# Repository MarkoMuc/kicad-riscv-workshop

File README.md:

# ESP32 board workshop

- Uradni repozitorij: https://github.com/bulicp/FRI-ESP32-PCB-workshop/tree/main

- Postavimo shemo. Kjer grupiramo komponente glede na funkcionalnost.
- Preko USB + USB C konektor zelimo da napajamo vse komponente na sistemi (procesor, ledice, itd.)

## Dan 1: USB-C in vse potrebne povezave.

Izhodisce je `00-template` iz git repozitorija delavnice:
- `.PCB`: printed circuit board.
- `.SCH`: schemas. Dve shemi: power and digital + schema, ki ju zdruzi.

Zaceli bomo z power:
- USB C in konektorji.
- Lahko se uporablja za napajanje, nekateri procesorji tudi uporablja za flashanje, v ta namem rabimo USB del povezave, ne le napajanje.

Komponente vpeljemo iz knjiznice komponent, ostale dodamo: Simboli in footprint.
- Simbol je samo simbol (za sheme).
- Footprint je odtis komponent na tiskanem vezju (kje se lota, prostor, tloris komponente).

Pritisni `a`, da odpres izbiro/dodajanje simbolov.
Nasa knjiznica je `fri`.

Zacnemo z USB konektorjem `USC_C_Receptacle_USB2.0_16P` iz `fri`.
Rdece blazinice so kjer se zalota.
Vidimo 11 povezav, a jih je v resnici 16.
Predstavljene so s zicko, ki se konca s krogom.
To je zato, kjer `VBUS` ima v resnici vec povezav?

Pini na USB-C konektorju:
- `VBUS` signal je zica, ki bo dostavila 5V, za napajanje.
    - Za vsak vir naptosti nas zanimata dve stvari: tok in moc.
    - USB C standard doloca 3 napajalne moci:
        - Vsaj 500mA toka in 5V napteost = 2,5 W.
        - Ter se drugi dve.
    - Za nas bo 500mA dovolj, a velikokrat potrebujemo vec. Sistemo mora vedeti koliko mu lahko oddaja napajlni vir.
        Npr. ce ni dovolj napajanja, se sistem naj ne bi brizgal. Kako pa to lahko ve?
        - Imamo dva pina `CC1` in `CC2`. Povesta ali napajlnik dostavlja 500 mA ali vec.
- `CC1` in `CC2` sta analogna, ne digitalna.
    - Odjamalec more vedeti s cim ga napaja. Obratno napajalnik mora vedeti porabo (ponor?).
        Npr. da ni samo `VBUS-GRND` povezava?
    - Potrebujemo 2 upora za delovanje napajanje (zaradi standarda).
        Dodamo upor z imenom simbola `R`.
        Prvi je `5.1K` povezan na `CC1`, isto naredimo za `CC2`.
        Spodnja dela uporov povezemo na `GND`.
- `SHIELD` in `GND` povezem na zemljo. To je lahko isti konektor za `GND`, locimo zato, da se zice ne krizajo.
- `SBUS1` in `SBUS2` ne rabimo, a je to potrebno povedati KiCad, tako da oznacimo, da prikljucek ni povezan.
    Pritisnemo `q` in povezemo na prikljucek.
- `D` prikljucki so diferencialni (komplementarni) prikljucki. Ko prenasam `0` je na `D_+: 1` in na `D_-: 0` ter obratno.
    To opravimo zaradi vpliva zunanjih dejavnikov (in posledicnega induciranega toka).
    Ce se napetost poveca zaradi šuma, se podobno zgodi na drugih zicah v blizini => signali po diferencialnih parih.
    Tako lahko locimo med `0` in `1` kljub sumu.
    Na primer vedno opravimo: `D_+ - D_-`.
    Po odstevanju se šum odstani.
    Tu imamo 4 pine, pri USB-C lahko zato vstavimo kabel ne glede na orientacijo.
- `VBUS` ima pri nas 5V, povezemo ga preko zice, ki nadaljuje na drugem listu (drugi shemi).
    To naredimo tako, da zico oznacimo (label).

Za vsako komponento moramo poiskati `footprint` in povedat kaksen je footprint, da lahko tiskamo.
Za upornike izberemo `R_01005_0402Metric`:
    - `0402` pomeni velikost (sirina) fizicnega rezistorja. Manjsi ko je, manj inducirane napetosti?
    - `_SMD` pomeni: surface mount device.

Vse komponente na vezju se prelije s lakom, ki ni prevoden.
USB-C konektor ni prelit, in je iz kovine.
Vezje je potrebno zasciti pred elektrostaticnem naboju, ki bi poskodoval komponente.
Zagotavlja se s komponentami, ki preosmerijo ta naboj v `GND`.
To komponento postavimo na zico iz `VBUS`, ki se sprozi ko je napetost vec kot 5V.

Uprabimo diodo, ki v neki tocki, ne glede na velikost toka, napetost ne spreminja.
Povezemo diodo `PESD5V0S1UL` in jo obrnemo z `r`, povezemo naprej na `GND` (spodnji del) ter na `VBUS` zico.

"Induciran kondenzator" je posledica vec plastne strukture cipov in komponent (plasti silicija).
Iscemo komponento z zelo nizko kapacitivnost, saj kodenzator deformira PWL signale (kot so podatkovni).
Pri nas uporabimo za zascito USB komponente, `USBLC6-2SC6`, na sliko lahko vidimo interno diodo, ki sciti.
Prikljucka `1-6` ter `3-4` sta ista. `5` gre na `VBUS`, `2` gre na `GND`.
Povezemo na `D_-` in `D_+` (ter iste povezave skupaj), dodamo globalne labele (pazi na ime naj se konca enako, mislim da KICAD to potrebuje).

Neko osnovno analizo vezja opravimo z `inspect - ERC`, ki nas opozori, da ni elektricnega vira.
Da ga eksplicitno ustvarimo, dodamo `PWR_FLAG`. Podobno naredimo tudi za `GND` (t.j. minus).

Nasledjni korak je sprememba 5V toka v 3.3V, ki ga sprejme ESP32.
Uporabi se DC/DC pretvornike, regulatorje, transformerje?
Za pretvorbo naptosti uporabimo regulator `XC6220B331MR`:
- Regulator ima pin za kontrolo `CE-Chip Enable`, ki ga prizge.
    To se opravi npr. ko je premajhna napetost (prazna baterija, da jo zascitimo).
- Mi ne rabimo CE, zato povezemo na VBUS z upornikom, ki naj bi bil po standardu 10K ohm.
Datasheet pravi, da potrebujemo se 2 kondenzatorja, eden za vhod, eden za izhod.
Pri kondenzatorjih je tezko dosesti pripisano kapacitivnost.
Zelimo cim manjsi footprint, tezje je kontrolikarti kapacitivnost (zaradi segrevanja itd.).
Manjsi footprint pomeni manjsa induktivnost.
Izberemo footprint `0805SMD`.
Ustvarili smo LDO 3.3V regulator. Ker se mocno segrevajo, je potrebno pravilno postaviti, da se pasivno ohlaja.

Uprabimo lahko tudi DC-DC konvertorji, ki so brezizgubni (oddajo jo v kondenzator, ko jo rabijo dvigniti, jo vzamejo iz kondenzatorja).
Sestavljajo jih tuljave.
Vsi cipi, vkljucno z nasim esp32, imajo DC-DC konverter (realiziran na cipu).
Dovod elektricne moci lahko tudi sestavlja notranja baterija, ter sistem, ki izbira med baterijo in direktno povezavo.

Sedaj imamo vse kar rabimo, da povezemo CPE, premaknemo se na `digital` shemo.
V nasem primeru imamo `esp32-C3-mini`, ki je RISC-V procesor.
Sicer je to SoC, kar pomeni, da ni samo procesor, temvec je modul.
Vsebuje anteno (za WIFI ter BLE), sistem za flashanje, RAM, itd.
Pricljucki na `ESP32-C3-MINI-1`:
- `3V3` in `GND` povezemo na +3.3V in zemljo.
- `EN` povezemo na label `EN`.
- `GPIO18/19` povezemo na `USBD+/-` labele.
- `GPIO21/20` povezemo na `TXD/RXD` labele.
- `GPIO3-5` povezemo na isto imenske labele.
- `GPIO6/7` sta vezana na LED diode.
- `GPIO2 + GPIO8 + GPIO9` so pri ESP32 kontrolni signali, ki povejo, da rabi CPE poiskati novo vrednost is flasha (ki je bil spremenjen?) za zagon.
    Imenujemo `GPIOX_BOOT`.
- `GPIO10` povezemo na labelo `USER_BTN`.

Zaceli bomo z ledicami:
- Ledice so tudi diode, sveti ko je V1 > V2 (kjer je V1 na strani (stranice) trikotnika).
- `V2` stran vezemo na GPIO pin, ker je to stran, ki je manjsa. To pomeni, da iz pina ne vlece toka.
    Tako je ta pin ponor, energija gre v ohisje.
    Drugace bi od CPE zahtevali veliko napetosti?
    Ce vezemo drugo stran (V1) na 3.3V, je problem v tem, da ni nobene upornosti na povezavi. Tok je zato lahko velik in naredi skodo.
    Ta tok je treba omeijti (z uporom). Upor dolocimo glede na datasheet ledice (razpon uporov/tokov).
    Mi izberemo 330 ohmov, manj ko je upora, bolj je svetla ledica.
- Ponovimo isto za `LED1`.

Nadaljujemo z gumbom:
- Uporabimo `SW_Push`.
- Mi zelimo, da ob pritisku na gumb, zaznamo niclo: `USER_BTN`.
    To je zaradi tega, ker je lazje iti iz 1 v 0?
    Drugi del vezemo na 3.3V, ter na nek upornik (drugace je kratki stik).
    Tako je brez pritiska 3.3V, ko pa pritisnemo gumb, gremo iz 3.3 proti ground.
    Ta tok se le porabi (direktno v zemljo), zelimo cim manjsi upor?
    To je pull-up upornik.
    Manjsi ko je upor, vec je vpliva suma, a je manjsi tok?
    Vecji upor, manj vpliva suma, visji tok??
    Izberemo 10k ohm.
- Isto za `EN` gumb na cipu (reset gumb).

Pini GPIO2,8,9:
- Za zagon preko flasha, za prenos v flash, itd.
- GPIO2 vedno 1.
- GPIO8 vedno 1.
- Ce je po reset: GPIO9 high, preberi program v flash.
- Ce je po reset: GPIO9 low, potem se pripravi na branje iz USB.
- To pomeni, da je pametno GPIO9 vezati na nek gumb.
- GPIO2 in GPIO8 lahko vezemo na 3.3V, uporabimo tudi upornik kot v primeru gumba.

Ostale GPIO prikljucke zelimo vezati na GPIO pin, ker so splosni za uporabo:
- Uporabimo `Conn_01x08` za 8 pinov, mi imamo 7 pinov prostih.
- Vrstni red ni pomemben, le lahko naredi koncno vezje kompleksno. Zato razporedimo GPIO cim lepse.
- Viska PIN vezemo na `GND`, ker je to vedno uporabno. Podobno tudi zelimo 3.3V za uporabo.
- Naredimo se en prikljucek, ki ima tri 3.3V pine, 4 x GND pine in 1 x VBUS (5.1V) pin.

Manjko nam se kondenzatorji na vseh napajalnih pinih.
Pri nas je to le eden.
Kondenzator ne sme biti velik (drugace vecji induciran tok?) ter mora biti cim blizje prikljucku.
Drugo pravilo je to, da vendo rabimo 2 kondenzatorja, drugi mora biti vecji (za dogodke, ki so daljsi kot 1ns).
Eden je `100nF`, drug je `10mF`.
Drugi kondenzator mora tudi imeti vecje ohisje (ker je vecji), tako izberemo drug footprint: `0402_1005` in `0805`.

Manjsi konenzator dodamo se drugod:
- Kjerkoli je gumb.

Footprints:
- `100nF` -> `0402_1005Metric`.
- `10uF` -> `0805_2012Metric`.

## Dan 2

`Tools - Bulk edit symbol fields` se uporablja za spreminjanje polj vseh simbolov v projektu.
Sprva bomo popravili vrednosti LED diod.

Vsak kondenzator ima induktivnost, manjsi imajo manjso, vecji visjo (zakaj je to pommebno, kva to pomen?)
Konektorji za pine normalno proizvalajec vezja ne doda, temvec samo opravi routing, nato sam zalotas konektor (oz pine).
Za `J2/J3` izberemo `Exclude from Bill Of Material` ter `Exclude from board`, to da proizvalajcu vedeti, da bomo opravili sami.
Na vsaki komponenti izberemo se `Do not populate`.
V polje `LCSC` vpisemo pripadajoco kodo izdelka na strani LCSC.
Dodamo lahko tudi `MPN` stevilko, to je identifikacijska stevila izdelka proizvalajca.
Previdno izberemo vse footprinte ter identifikacijske stevilke komponent.

Nasledjni korak je ustvariti pravo vezje.
Razvoj se nadalje opravlja v oknu `Switch PCB editor`.

Tiskano vezje je sestavljeno iz vec plasti:
- `.Cu` so bakrene plasti.
- Tiskanje (crke, znaki) je ena plast.
- Plast za masko.
- Plast za silk screen.
- Plast edge cuts (zunanji obris).
- Itd.

Preden lahko risemo izberemo plast.
Zacnemo z `Edge.cuts` in narisemo zeljene dimenzije vezja, na templatu je to ze narejeno.
Sprva prenesemo vse footprinte iz shem: `Update PCB from Schematic`.
Kako postavimo komponente ni strogo doloceno, moramo pa razmisliti o vlogi neke komponente in
postaviti logicno glede na to (npr. USB na rob itd.).
Na zectku pri premikanju izberemo samo `footprint`, da premaknemo vse.
Komponente vedno postavljamo na `F.Cu`: `Front Cu`.
Zakaj imamo 4 bakrene plasti?:
- Na vsaki bakreni plasti risemo linije.
- Vec kot je plasti, tezke je risanje linij, vezja so vecja, jumperji (resitev za krizajne zick), itd.
- `via`- "luknje", ki omogocajo prehajanje med plastmi.
- Danes imajo vsa vezja vsaj 2 plasti:sprednja in zadnja.
    - Pri dvo plastnih je tezava s pozicijo `GND` lokacij (dolge povratne poti),
        to resijo tako, da vsaki plasti dodamo se eno `GND` plast, oznaceni kot `In1.Cu`.
    - Velika prevodna plast, z majhno induktivnostjo?
    - Velikokrat je se dodatna `GND` plast, ki loci `power` in `data` plasti.
- `F.Cu` so signali, `In1.Cu` je `GND plane`, `In2.Cu` je `power plane`, `B.Cu` je signal plane.
- Danes je vecinoma minimalno 4 plasti.
- Pri RAMu nujno rabimo istocasne signale is procesorja, vsi signali morajo imeti isto inpendanco?, zato imajo svojo plast?

Pri nas:
- `F.Cu`: vse komponente.
- `In1.Cu`: `GND`.
- `In2.Cu`: power.
- `B.Cu`: probamo izogniti.

Na zacetku postavljamo funkcionalne bloke.
Ko postavljamo `GND` blazinice si zelimo najkrajse povezave (uporabimo `GND` plast).
Dodamo tudi fiduciale, to so krogci, ki pomagajo stroju, da se orientira.
Nato na `In1.Cu` dodamo `Filed zone`.
V `Board setup` nastavimo dimenzije vij, ter zick.
Nato narisemo poligon za `VBUS` na `In2.Cu`.
Povezave se vendo rise na `F.Cu`.

`USBD-` in `USBD+` sta diferencialna signala in morata priditi do CPE istocasno!
To pomeni, da morata biti obe zici enaki (po dolzini, in obliki, kolikor se seveda da to narediti).
Uporabi `Route - Route differential pair`.
Ko imamo dve zoni na isti plasti, on sprva zrise zone z visjo prioriteto.

Pri CPE se moramo zavedati, da je `Antenna Area` svoja cona, pod njo (ter L in D od nje), ne sme biti kovine.
Definiramo `Keep out` cone.

Zice po katerih gredo (okoli 1 Mb na sekundo) ne prekrivamo z viami.
Dodatno pravilo je, da cim vec zapolni z `GND` polju.

## Dan 3

Ne zelimo `GND` otokov.
Napovnemo ostali prostor z viami.

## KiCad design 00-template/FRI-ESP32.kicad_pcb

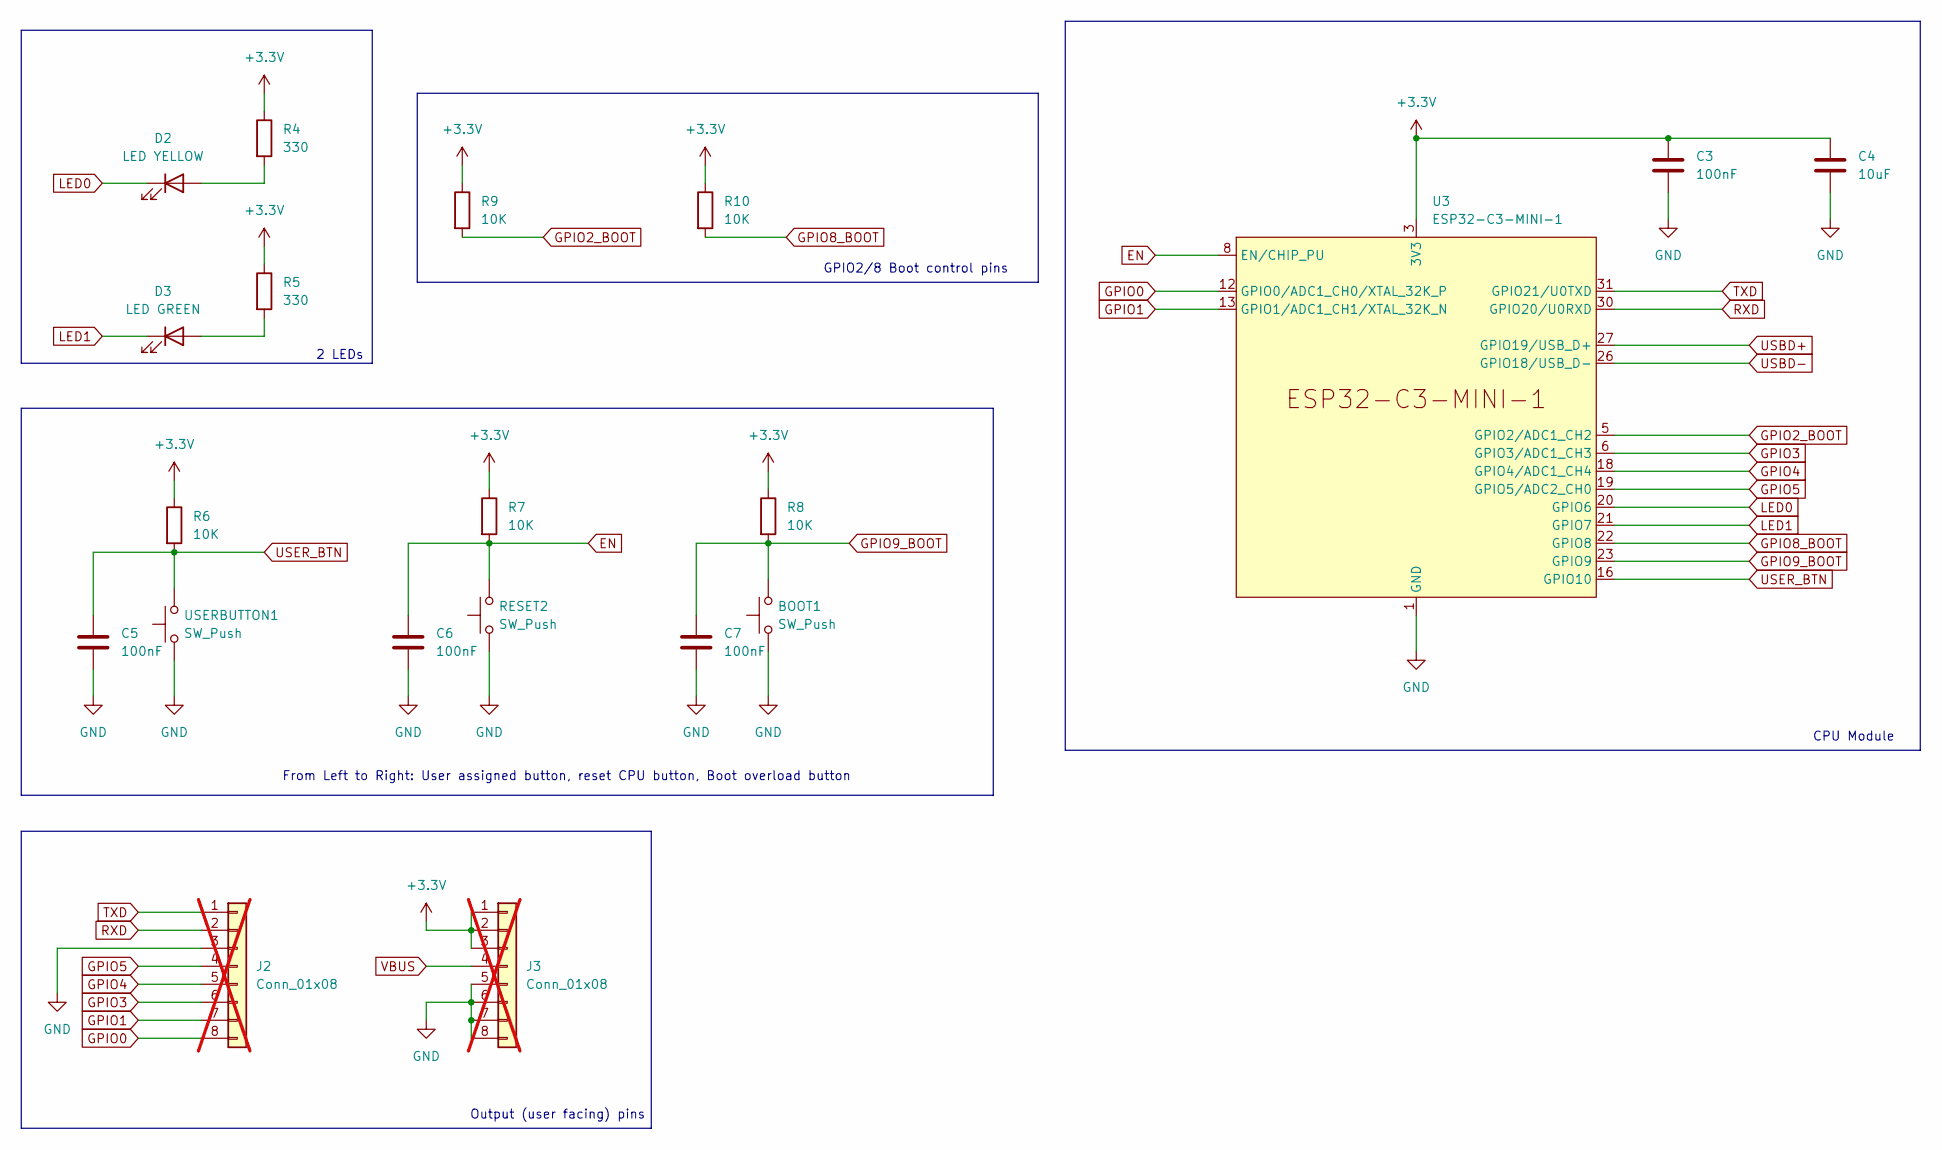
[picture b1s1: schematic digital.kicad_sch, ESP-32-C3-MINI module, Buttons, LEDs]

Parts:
BOOT1: SW_Push; SW_SPST_B3U-1000P-B; MPN B3U-1000P; LCSC C231329
C3, C5, C6, C7: 100nF; C_0402_1005Metric
C4: 10uF; C_0805_2012Metric
D2: LED YELLOW; LED_0805_2012Metric; LCSC C2297
D3: LED GREEN; LED_0805_2012Metric; LCSC C2297
J2, J3: Conn_01x08; PinHeader_1x08_P2.54mm_Vertical; not fitted
R4, R5: 330; R_0402_1005Metric
R6, R7, R8, R9, R10: 10K; R_0402_1005Metric
RESET2: SW_Push; SW_SPST_B3U-1000P-B; MPN B3U-1000P; LCSC C231329
U3: ESP32-C3-MINI-1; MPN ESP32-C3-MINI-1-N4; LCSC C2838502
USERBUTTON1: SW_Push; SW_SPST_B3U-1000P-B; MPN B3U-1000P; LCSC C231329

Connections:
+3.3V: C3.1, C4.1, J3.1, J3.2, J3.3, R4.1, R5.1, R6.1, R7.1, R8.1, R9.1, R10.1, U3.3 (3V3); also elsewhere on the board
EN: C6.1, R7.2, RESET2.2, U3.8 (EN/CHIP_PU)
GND: BOOT1.1, C3.2, C4.2, C5.2, C6.2, C7.2, J2.3, J3.5, J3.6, J3.7, J3.8, RESET2.1, U3.1 (GND), U3.2 (GND), U3.11 (GND), U3.14 (GND), U3.36 (GND), U3.37 (GND), U3.38 (GND), U3.39 (GND), U3.40 (GND), U3.41 (GND), U3.42 (GND), U3.43 (GND), U3.44 (GND), U3.45 (GND), U3.46 (GND), U3.47 (GND), U3.48 (GND), U3.49 (GND), U3.50 (GND), U3.51 (GND), U3.52 (GND), U3.53 (GND), USERBUTTON1.1; also elsewhere on the board
GPIO0: J2.8, U3.12 (GPIO0/ADC1_CH0/XTAL_32K_P)
GPIO1: J2.7, U3.13 (GPIO1/ADC1_CH1/XTAL_32K_N)
GPIO2_BOOT: R9.2, U3.5 (GPIO2/ADC1_CH2)
GPIO3: J2.6, U3.6 (GPIO3/ADC1_CH3)
GPIO4: J2.5, U3.18 (GPIO4/ADC1_CH4)
GPIO5: J2.4, U3.19 (GPIO5/ADC2_CH0)
GPIO8_BOOT: R10.2, U3.22 (GPIO8)
GPIO9_BOOT: BOOT1.2, C7.1, R8.2, U3.23 (GPIO9)
LED0: D2.1 (K), U3.20 (GPIO6)
LED1: D3.1 (K), U3.21 (GPIO7)
unnamed: D2.2 (A), R4.2
unnamed: D3.2 (A), R5.2
RXD: J2.2, U3.30 (GPIO20/U0RXD)
TXD: J2.1, U3.31 (GPIO21/U0TXD)
USBD+: U3.27 (GPIO19/USB_D+); also elsewhere on the board
USBD-: U3.26 (GPIO18/USB_D-); also elsewhere on the board
USER_BTN: C5.1, R6.2, U3.16 (GPIO10), USERBUTTON1.2
VBUS: J3.4; also elsewhere on the board

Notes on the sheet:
Output (user facing) pins
GPIO2/8 Boot control pins
2 LEDs
CPU Module
From Left to Right: User assigned button, reset CPU button, Boot overload button

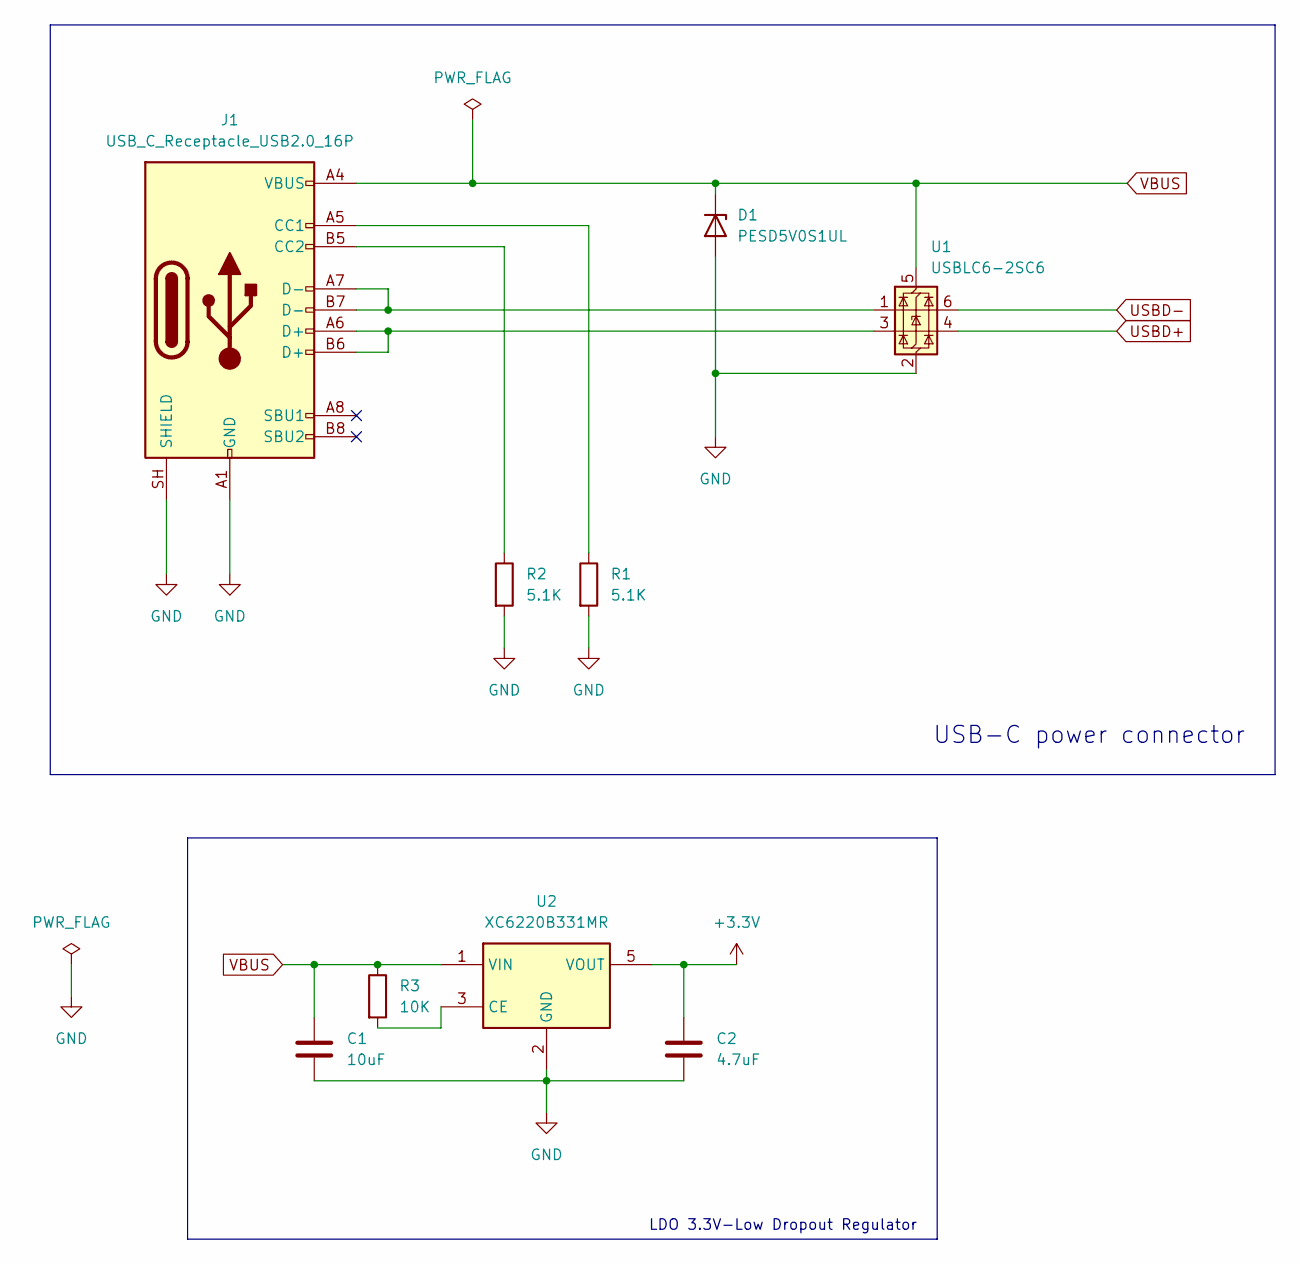
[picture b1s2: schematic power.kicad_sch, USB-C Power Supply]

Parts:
C1: 10uF; C_0805_2012Metric
C2: 4.7uF; C_0805_2012Metric
D1: PESD5V0S1UL; D_SOD-882
J1: USB_C_Receptacle_USB2.0_16P; USB_C_Receptacle_G-Switch_GT-USB-7010ASV; MPN GT-USB-7010ASV; LCSC C2988369
R1, R2: 5.1K; R_0402_1005Metric
R3: 10K; R_0402_1005Metric
U1: USBLC6-2SC6; SOT-23-6; LCSC C7519
U2: XC6220B331MR; SOT-23-5

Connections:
+3.3V: C2.1, U2.5 (VOUT); also elsewhere on the board
GND: C1.2, C2.2, D1.2 (A), J1.A1 (GND), J1.A12 (GND), J1.B1 (GND), J1.B12 (GND), J1.SH (SHIELD), R1.2, R2.2, U1.2 (GND), U2.2 (GND); also elsewhere on the board
unnamed: J1.A5 (CC1), R1.1
unnamed: J1.B5 (CC2), R2.1
unnamed: J1.A6 (D+), J1.B6 (D+), U1.3 (I/O2)
unnamed: J1.A7 (D-), J1.B7 (D-), U1.1 (I/O1)
unnamed: R3.2, U2.3 (CE)
USBD+: U1.4 (I/O2); also elsewhere on the board
USBD-: U1.6 (I/O1); also elsewhere on the board
VBUS: C1.1, D1.1 (K), J1.A4 (VBUS), J1.A9 (VBUS), J1.B4 (VBUS), J1.B9 (VBUS), R3.1, U1.5 (VBUS), U2.1 (VIN); also elsewhere on the board

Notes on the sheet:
LDO 3.3V-Low Dropout Regulator
USB-C power connector

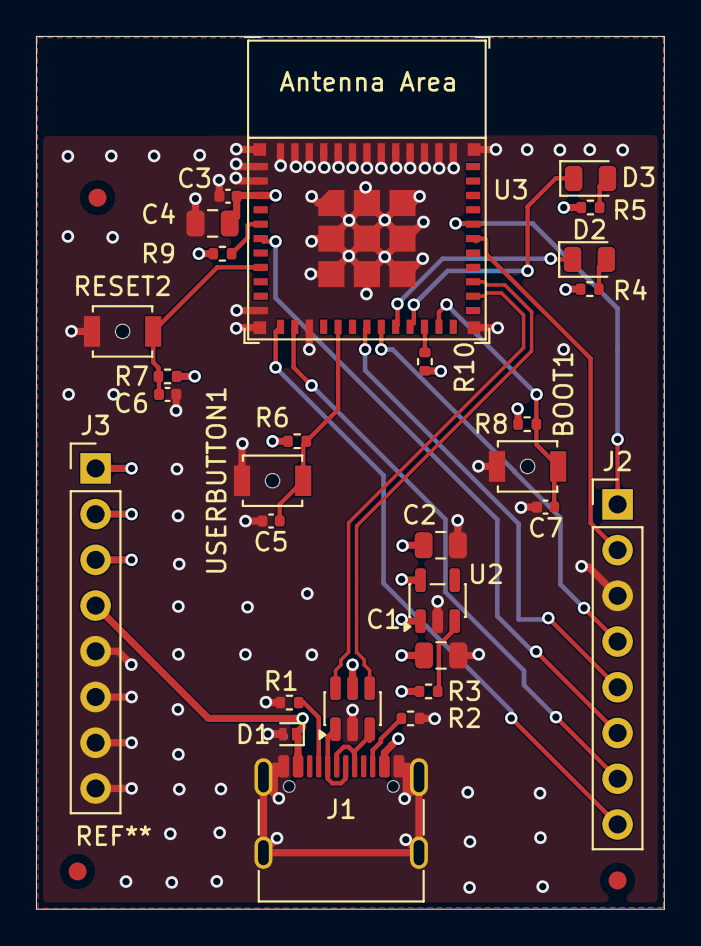
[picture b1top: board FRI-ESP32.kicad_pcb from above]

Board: 4 copper layers, 34.9 x 48.5 mm, 30 parts (1 on the bottom side), 26 nets.

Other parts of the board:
CC: LOGO; CCChipSI12x6

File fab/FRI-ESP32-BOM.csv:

"Reference","Qty","Value","DNP","Exclude from BOM","Exclude from Board","Footprint","Datasheet","Purpose","Description","#","LCSC","MPN"
"BOOT1,RESET2,USERBUTTON1","3","SW_Push","","","","fri:SW_SPST_B3U-1000P-B","","","Push button switch, generic, two pins","1","C231329","B3U-1000P"
"C1,C4","2","10uF","","","","Capacitor_SMD:C_0805_2012Metric","","","Unpolarized capacitor","2","",""
"C2","1","4.7uF","","","","Capacitor_SMD:C_0805_2012Metric","","","Unpolarized capacitor","3","",""
"C3,C5,C6,C7","4","100nF","","","","Capacitor_SMD:C_0402_1005Metric","","","Unpolarized capacitor","4","",""
"D1","1","PESD5V0S1UL","","","","Diode_SMD:D_SOD-882","https://assets.nexperia.com/documents/data-sheet/PESD5V0S1UL.pdf","","Unidirectional ESD protection diode, 5V, SOD-882","5","",""
"D2","1","LED YELLOW","","","","LED_SMD:LED_0805_2012Metric","","","Light emitting diode","6","C2297",""
"D3","1","LED GREEN","","","","LED_SMD:LED_0805_2012Metric","","","Light emitting diode","7","C2297",""
"J1","1","USB_C_Receptacle_USB2.0_16P","","","","fri:USB_C_Receptacle_G-Switch_GT-USB-7010ASV","https://www.usb.org/sites/default/files/documents/usb_type-c.zip","","USB 2.0-only 16P Type-C Receptacle connector","8","C2988369","GT-USB-7010ASV"
"R1,R2","2","5.1K","","","","Resistor_SMD:R_0402_1005Metric","","","Resistor","9","",""
"R3,R6,R7,R8,R9,R10","6","10K","","","","Resistor_SMD:R_0402_1005Metric","","","Resistor","10","",""
"R4,R5","2","330","","","","Resistor_SMD:R_0402_1005Metric","","","Resistor","11","",""
"U1","1","USBLC6-2SC6","","","","fri:SOT-23-6","https://www.st.com/resource/en/datasheet/usblc6-2.pdf","","Very low capacitance ESD protection diode, 2 data-line, SOT-23-6","12","C7519",""
"U2","1","XC6220B331MR","","","","fri:SOT-23-5","https://www.torexsemi.com/file/xc6220/XC6220.pdf","","1A, Low Drop-out Voltage Regulator, Fixed Output 3.3V, SOT-23-5","13","",""
"U3","1","ESP32-C3-MINI-1","","","","fri:ESP32-C3-MINI-1","https://www.espressif.com/sites/default/files/documentation/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","","ESP32-C3-MINI-1 family is an ultra-low-power MCU-based SoC solution that supports 2.4 GHz Wi-Fi and Bluetooth®Low Energy (Bluetooth LE).","14","C2838502","ESP32-C3-MINI-1-N4"
